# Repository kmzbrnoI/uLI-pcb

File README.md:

uLI – Ultimate LI PCB
=====================

uLI is a XpressNET &#8596; USB converter behaving as COM port in PC (CDC).

## uLI v5

* Designed in: KiCad 7
* Main Processor: PIC18F14K50
* Several enhancements from uLI v4, backward-compatible.
  - See releases/tags for a list of modifications from uLI v4.
* Firmware is same for v4 & v5.
* Authors: Jan Horacek (c) 2024

## uLI v4

* Deprecated.
* Designed in: Eagle 9
* Main Processor: PIC18F14K50
* Authors: Jan Horacek, Michal Petrilak (c) 2016

## Firmware

* [uLI-fw](https://github.com/kmzbrnoI/uLI-fw)
* [uLI-master-fw](https://github.com/kmzbrnoI/uLI-master-fw)

## Further reading

- [About XpressNET](http://www.opendcc.de/info/xpressnet/xpressnet_e.html)
- uLI meets [XpressNET specification v3](http://www.lenzusa.com/1newsite1/Manuals/xpressnet.pdf)
- uLI should also meet [XpressNET specification v3.6](http://wiki.rocrail.net/lib/exe/fetch.php?id=xpressnet-en&cache=cache&media=xpressnet:xpressnet-lan-usb-23151-v1.pdf) (available only in German)

## License

Content of the repository is provided under [Creative Commons
Attribution-ShareAlike 4.0
License](https://creativecommons.org/licenses/by-sa/4.0/) as openhardware
project. You may download any data, contribute to the project, create PCB
yourself or even sell it yourself.

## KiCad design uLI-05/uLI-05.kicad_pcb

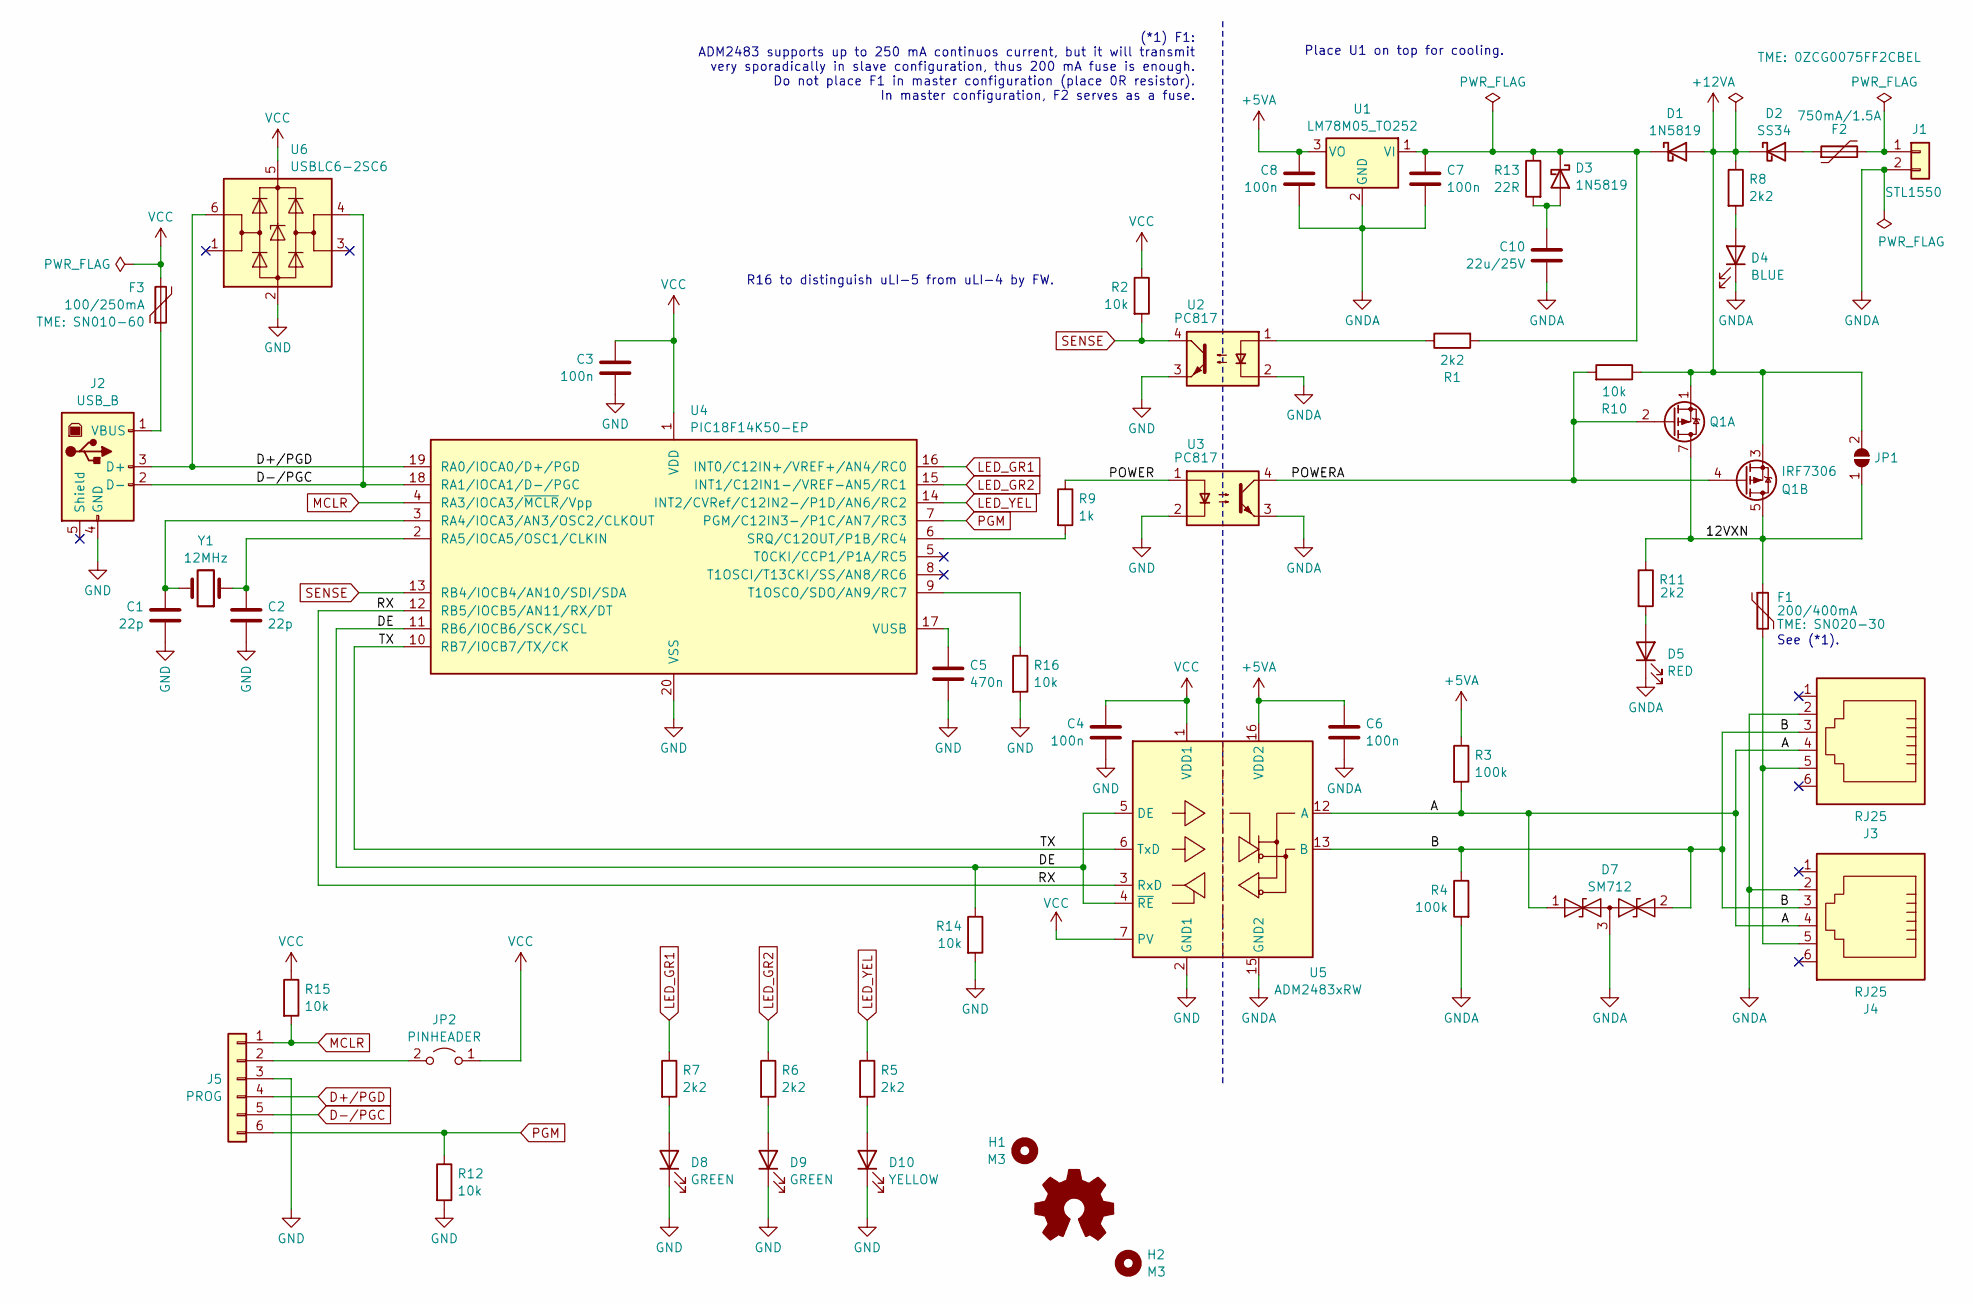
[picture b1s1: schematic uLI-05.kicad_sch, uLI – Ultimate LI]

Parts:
C1, C2: 22p; C_0805_2012Metric; LCSC C1804
C3, C4, C6, C7, C8: 100n; C_0805_2012Metric; LCSC C49678
C5: 470n; C_0805_2012Metric; LCSC C13967
C10: 22u/25V; C_0805_2012Metric; LCSC C45783
D1, D3: 1N5819; D_SOD-123; LCSC C8598
D2: SS34; D_SMA; LCSC C8678
D4: BLUE; LED_D3.0mm; JLCPCB_IGNORE true
D5: RED; LED_D3.0mm; JLCPCB_IGNORE true
D7: SM712; SOT-23; LCSC C32677
D8, D9: GREEN; LED_D3.0mm; JLCPCB_IGNORE true
D10: YELLOW; LED_D3.0mm; JLCPCB_IGNORE true
F1: 200/400mA; Fuse_1206_3216Metric; JLCPCB_IGNORE true
F2: 750mA/1.5A; Fuse_1812_4532Metric; JLCPCB_IGNORE true
F3: 100/250mA; Fuse_1206_3216Metric; JLCPCB_IGNORE true
H1, H2: M3; MountingHole_3.2mm_M3_Pad; JLCPCB_IGNORE true
J1: STL1550; PhoenixContact_MC_1,5_2-G-3.5_1x02_P3.50mm_Horizontal; JLCPCB_IGNORE true
J2: USB_B; USB_B_OST_USB-B1HSxx_Horizontal; JLCPCB_IGNORE true
J3, J4: RJ25; RJ12_Amphenol_54601-x06_Horizontal; JLCPCB_IGNORE true
J5: PROG; PinHeader_1x06_P2.54mm_Vertical; JLCPCB_IGNORE true
JP1: SolderJumper-2_P1.3mm_Open_RoundedPad1.0x1.5mm; JLCPCB_IGNORE true
JP2: PINHEADER; PinHeader_1x02_P2.54mm_Vertical; JLCPCB_IGNORE true
Q1: IRF7306; SOIC-8_3.9x4.9mm_P1.27mm; LCSC C879047
R1, R5, R6, R7, R8, R11: 2k2; R_0805_2012Metric; LCSC C17520
R2, R10, R12, R14, R15, R16: 10k; R_0805_2012Metric; LCSC C17414
R3, R4: 100k; R_0805_2012Metric; LCSC C149504
R9: 1k; R_0805_2012Metric; LCSC C17513
R13: 22R; R_0805_2012Metric; LCSC C17561
U1: LM78M05_TO252; TO-252-2; JLCPCB_IGNORE true
U2, U3: PC817; DIP-4_W7.62mm; JLCPCB_IGNORE true
U4: PIC18F14K50-EP; SSOP-20_5.3x7.2mm_P0.65mm; LCSC C12460
U5: ADM2483xRW; SOIC-16W_7.5x10.3mm_P1.27mm; LCSC C386280
U6: USBLC6-2SC6; SOT-23-6; JLCPCB_IGNORE true
Y1: 12MHz; Crystal_HC49-4H_Vertical; JLCPCB_IGNORE true

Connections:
+5VA: C6.1, C8.1, R3.1, U1.3 (VO), U5.16 (VDD2)
+12VA: D1.2 (A), D2.1 (K), JP1.2 (B), Q1.1 (S1), Q1.3 (S2), R8.1, R10.1
/12VXN: F1.1, JP1.1 (A), Q1.5 (D2), Q1.6 (D2), Q1.7 (D1), Q1.8 (D1), R11.1
/A: D7.1 (A1), J3.4, J4.4, R3.2, U5.12 (A)
/B: D7.2 (A2), J3.3, J4.3, R4.1, U5.13 (B)
/DE: R14.1, U4.11 (RB6/IOCB6/SCK/SCL), U5.4 (~RE), U5.5 (DE)
/POWER: R9.1, U3.1
/POWERA: Q1.2 (G1), Q1.4 (G2), R10.2, U3.4
/RX: U4.12 (RB5/IOCB5/AN11/RX/DT), U5.3 (RxD)
/TX: U4.10 (RB7/IOCB7/TX/CK), U5.6 (TxD)
D+/PGD: J2.3 (D+), J5.4, U4.19 (RA0/IOCA0/D+/PGD), U6.6 (I/O1)
D-/PGC: J2.2 (D-), J5.5, U4.18 (RA1/IOCA1/D-/PGC), U6.4 (I/O2)
GND: C1.1, C2.1, C3.2, C4.2, C5.2, D8.1 (K), D9.1 (K), D10.1 (K), J2.4 (GND), J5.3, R12.2, R14.2, R16.2, U2.3, U3.2, U4.20 (VSS), U5.2 (GND1), U5.8 (GND1), U6.2 (GND)
GNDA: C6.2, C7.2, C8.2, C10.2, D4.1 (K), D5.1 (K), D7.3 (common), J1.2, J3.2, J4.2, R4.2, U1.2 (GND), U2.2, U3.3, U5.9 (GND2), U5.15 (GND2)
LED_GR1: R7.1, U4.16 (INT0/C12IN+/VREF+/AN4/RC0)
LED_GR2: R6.1, U4.15 (INT1/C12IN1-/VREF-AN5/RC1)
LED_YEL: R5.1, U4.14 (INT2/CVRef/C12IN2-/P1D/AN6/RC2)
MCLR: J5.1, R15.2, U4.4 (RA3/IOCA3/~MCLR/Vpp)
unnamed: C7.1, D1.1 (K), D3.1 (K), R1.2, R13.1, U1.1 (VI)
unnamed: D2.2 (A), F2.1
unnamed: C10.1, D3.2 (A), R13.2
unnamed: D4.2 (A), R8.2
unnamed: D5.2 (A), R11.2
unnamed: D8.2 (A), R7.2
unnamed: D9.2 (A), R6.2
unnamed: D10.2 (A), R5.2
unnamed: F1.2, J3.5, J4.5
unnamed: F2.2, J1.1
unnamed: F3.1, J2.1 (VBUS)
unnamed: J5.2, JP2.2 (B)
unnamed: R1.1, U2.1
unnamed: C1.2, U4.3 (RA4/IOCA3/AN3/OSC2/CLKOUT), Y1.2
unnamed: C2.2, U4.2 (RA5/IOCA5/OSC1/CLKIN), Y1.1
unnamed: R9.2, U4.6 (SRQ/C12OUT/P1B/RC4)
unnamed: R16.1, U4.9 (T1OSCO/SDO/AN9/RC7)
unnamed: C5.1, U4.17 (VUSB)
PGM: J5.6, R12.1, U4.7 (PGM/C12IN3-/P1C/AN7/RC3)
SENSE: R2.2, U2.4, U4.13 (RB4/IOCB4/AN10/SDI/SDA)
VCC: C3.1, C4.1, F3.2, JP2.1 (A), R2.1, R15.1, U4.1 (VDD), U5.1 (VDD1), U5.7 (PV), U6.5 (VBUS)

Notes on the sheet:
R16 to distinguish uLI-5 from uLI-4 by FW.
Place U1 on top for cooling.
See (*1).
(*1) F1: ADM2483 supports up to 250 mA continuos current, but it will transmit very sporadically in slave configuration, thus 200 mA fuse is enough. Do not place F1 in master configuration (place 0R resistor). In master configuration, F2 serves as a fuse.

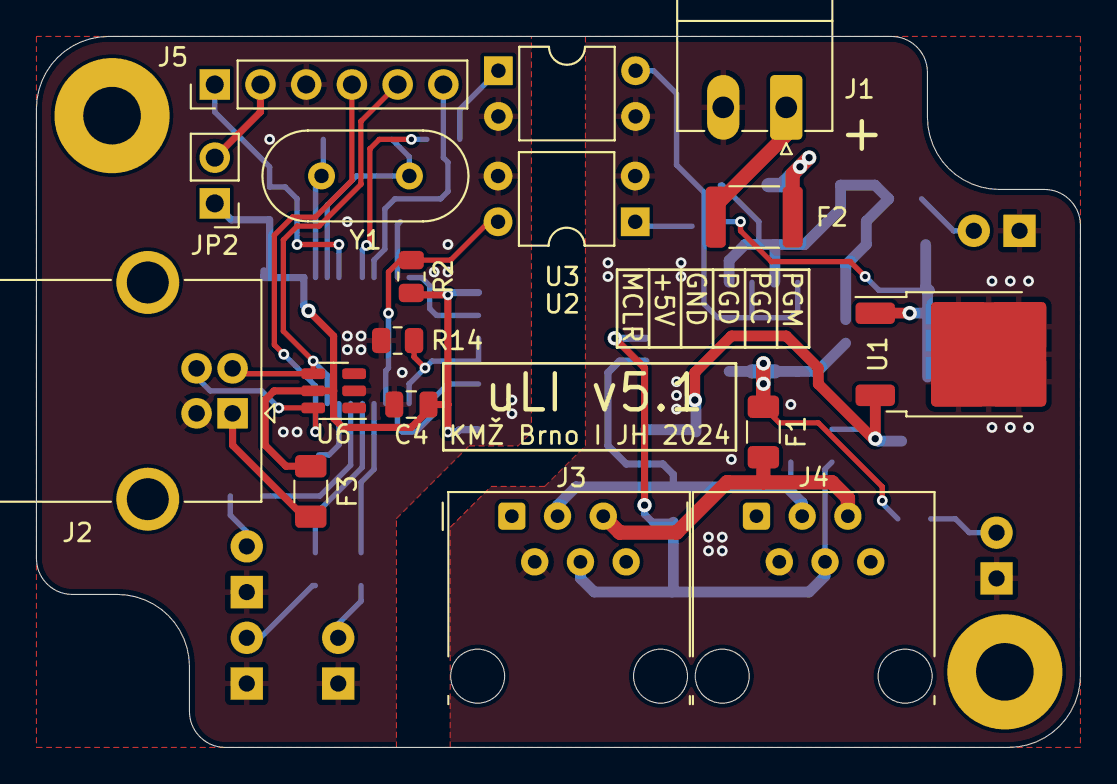
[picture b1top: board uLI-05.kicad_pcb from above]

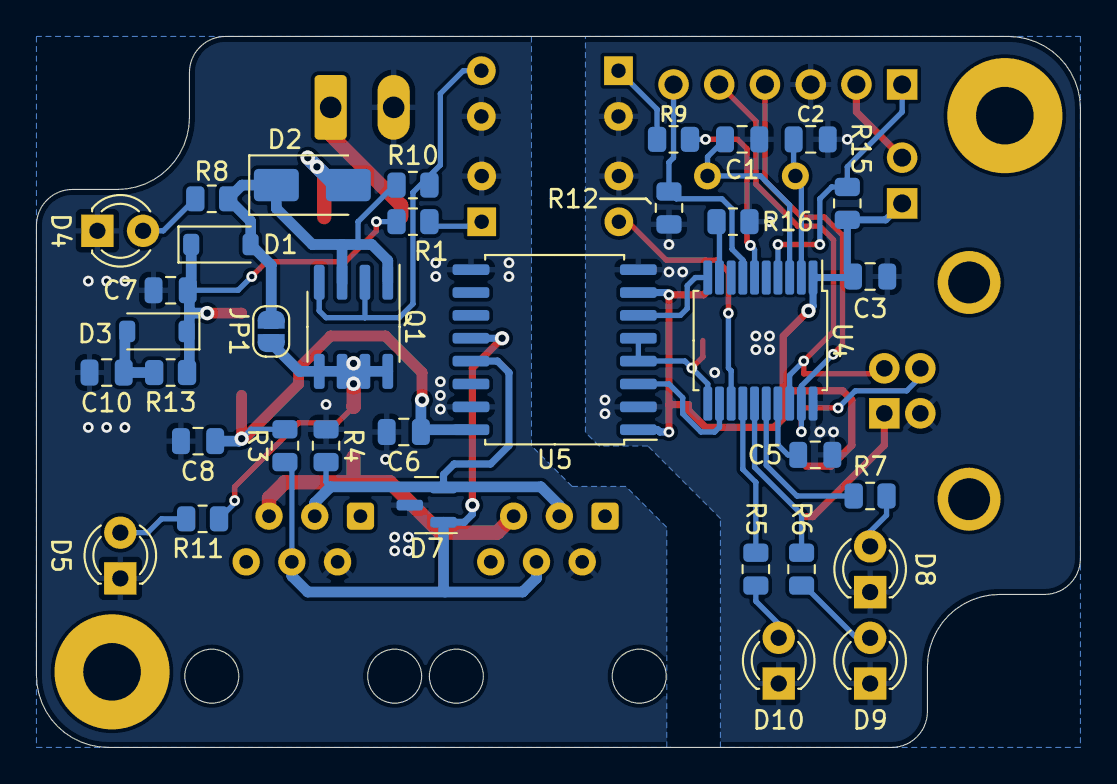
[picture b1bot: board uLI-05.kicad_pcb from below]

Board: 2 copper layers, 58.0 x 39.5 mm, 54 parts (35 on the bottom side), 39 nets.

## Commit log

2016-05-23 Initial commit.
2016-05-23 Fix readme.
2016-06-12 Napajeci spoje ztlusteny na 0.4 mm.
2016-06-12 Pouzito DRU seedstudio.
2016-06-12 Odstranen prebytecny kondenzator 100 n.
2016-06-12 Presunuty popisky soucastek.
2016-06-12 Obrys krabicky presunut do vrstvy "krab".
2016-06-12 DRU -> electrow.
2016-08-14 Upraven osazovak.
2016-08-15 uLI-04 rev 2.
    Opraveny chyby uLI-04 zjistene behem testovani:
    * upraven obrys krabicky podle realnych rozmeru (zvetseno symtetricky 1 mm do sirky a 0.5 mm do vysky)
    * posunuty otvory pro srouby do krabicky o 0.5 mm v kazde ose smerrem ke kraji
    * prohozeno RX a TX mezi procesorem a ADUMem
    * opraveno zdcadlove zapojeni XpressNETich konektoru
2016-08-16 Odstranena ochrana dioda na vstupu z USB.
2016-08-17 Omezeni proudovych razu - schema
    Pridan na schema rezistor a zmensen kondenzator pred stabilizator.
    Editovano jen schema. Deska neupravena.
2016-08-17 Pridan brown-out reset pro PV pin
    Jen schema.
2016-08-21 Doplnena data pro frezovani krabicky.
2016-08-22 Dokreslen rezistor 22 Ohm.
2016-08-22 Dokreslen brown-down obvod do DPS.
2016-08-22 Upravena hodnota kondenzatoru XN na 22uF.
2016-08-22 Variantni zapojeni nabijeciho rezistoru.
2016-08-27 6-4 > 6-6, ploska J5.
    * Konektory WEBP 6-4 nahrazeny za WEBP 6-6. Close #3.
    * Pajeci ploska pobliz J5 odstranena. Close 2.
2016-08-27 Progrmaovaci konektor posunut o 0.5 mm doleva.
    Close #7.
2016-08-27 Odstranen kus dratu u stabilizatoru.
    Close #6.
2016-08-27 Posunut C5.
    Close $5.
2016-08-27 Velikost vnejsiho okraje prokovu -> 0.9 mm.
    Close #4.
2016-08-29 Drobne zmeny.
    * Upraveno DRC na bezpecnejsi mezery.
    * Prokovy nastaveny globalne na 0.4 mm.
    * Posunuta dioda S2M.
2016-08-29 Upraveny pozice hodnot a nazvu soucastek.
2016-08-29 Doplnen nepropojeny vodic.
2016-09-27 Doplnen rezistor 10k na pin PGM (#9).
2016-09-27 Rev3.
2016-09-27 Update README.
2017-10-16 Add colors of LEDs.
2017-10-16 Do not use optoislators in slave variant.
2017-10-16 Do blue LED in slave variant.
2017-10-27 Move texts in mounting scheme.
2017-10-29 Add note about CNC XY origin.
2018-08-01 Remove unused uLI boards.
2019-03-13 Add .NC files for box production.
2019-03-13 CNC: add notes to README.
2019-03-15 Change value of LED resistors based on reality.
2019-03-15 Update Eagle to v9.
2019-03-15 Set precise MCP's voltage.
2021-02-23 Minor board tweaks.
2024-02-15 Add uLI-05 KiCad empty project.
2024-02-15 Copy schematics from uLI-04.
    Changes compared to uLI-04:
    * Add SM712 protection to Ale asiXpressNET
    * Add ESDA6V1 protection to USB
    * Change prog connector pnout to match PICKit
    * Unify pull-ups to 10k
    * Connect ADM2483's PV directly to VCC
2024-02-15 Add another diode to power supply.
    So XpressNET devices do not drain our internal capacitors.
2024-02-15 Add mounting holes, use 1N5819 as schottky diodes.
2024-02-15 Add option to bridge IRF7306 (slave variant).
2024-02-15 Add DE pull-down.
2024-02-17 Use part names from uLI-04.
2024-02-17 Add footprints.
2024-02-17 Use USBLC6 for USB protection.
    Benefits:
    * USBLC6 is specifically designed for USB
    * It also protects VCC
2024-02-17 Add R16 distinguish resistor.
    To distinguish between uLI-4 & uLI-5 in firmware.
2024-02-18 pcb: import mechanical from uLI-4, draw outline.
2024-02-18 pcb: place connectors & LEDs.
    Place on same positions as in uLI-4.
2024-02-18 Add STL1550 power connector.
2024-02-18 pcb: wire USB part.
2024-02-19 pcb: wire XpressNET part.
2024-02-20 Add vias.
2024-02-20 Tweak silkscreen.
2024-02-20 Add LCSC numbers.
2024-02-20 Fix issues reported by DRC.
2024-02-22 Add fuses.
2024-02-24 Use SS34 as D2.
    SS34 supports larger maximum current.
2024-02-29 F1, F2, F3: add JLCPCB_IGNORE.
2024-02-29 Move uLI-04 data to 'uLI-04' directory.
2024-02-29 D1, D2: add JLCPCB_CORRECTION.
2024-02-29 Remove misplaced wire.
2024-02-29 Change 1N5819 LCSC.
2024-03-01 Add v5 to README.
2024-03-23 Use 3.0 drills for RJ12 connectors.
    So the RJ12 connectors fit into the holes more precisely.
2024-03-24 Fix C6 position.
    Was outside of the board, move to appropriate place.

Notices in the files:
uLI-05/uLI-05.kicad_sch:
Released under the Creative Commons Attribution-ShareAlike 4.0 License
